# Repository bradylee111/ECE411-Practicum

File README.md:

# ECE411-Practicum

Top project Idea

Spinning music box
mechanically programmable

The idea is to use a photosensor array to read a spinning punch card with light shining through.
Using an ATmega328

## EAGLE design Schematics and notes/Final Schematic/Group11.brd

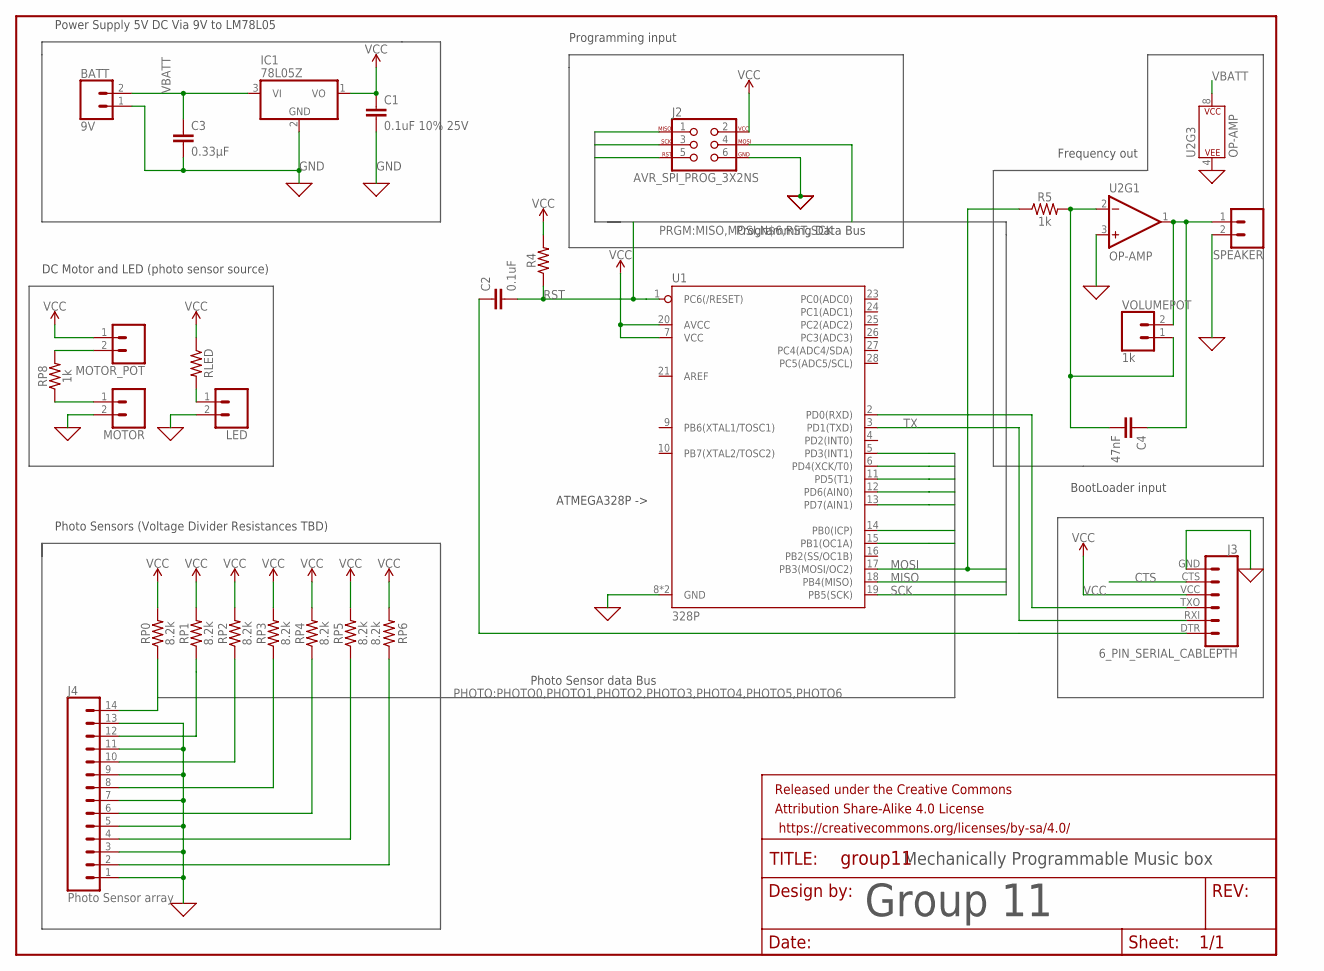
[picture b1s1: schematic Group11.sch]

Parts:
BATT: 9V; 1X02
C1: 0.1uF 10% 25V; 0603
C2: 0.1uF; 0603
C3: 0.33µF; 0805
C4: 47nF; 0603
FRAME1: FRAME-LETTER; CREATIVE_COMMONS
IC1: 78L05Z; TO92
J2: AVR_SPI_PROG_3X2NS; 2X3-NS
J3: 6_PIN_SERIAL_CABLEPTH; FTDI_BASIC
J4: Photo Sensor array; 1X14
LED: CONN_02; 1X02
MOTOR: CONN_02; 1X02
MOTOR_POT: CONN_02; 1X02
R4: 0805
R5: 1k; 0603
RLED: 0603
RP0, RP1, RP2, RP3, RP4, RP5, RP6: 8.2k; 0603
RP8: 1k; 0603
SPEAKER: CONN_02; 1X02
U1: 328P; DIP28
U2: OP-AMP; DIP08
VOLUMEPOT: 1k; 1X02

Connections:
CTS: J3.CTS (5)
GND: BATT.1, C1.2, C3.2, IC1.2 (GND), J2.6, J3.GND (6), J4.1, J4.3, J4.5, J4.7, J4.9, J4.11, J4.13, LED.2, MOTOR.2, SPEAKER.2, U1.8 (GND), U1.22 (GND), U2.3 (+IN), U2.4 (P$V-)
MISO: J2.1, U1.18 (PB4(MISO))
MOSI: J2.4, R5.1, U1.17 (PB3(MOSI/OC2))
unnamed: MOTOR_POT.2, RP8.2
unnamed: LED.1, RLED.2
unnamed: J3.TXO (3), U1.2 (PD0(RXD))
unnamed: C2.1, J3.DTR (1)
unnamed: MOTOR.1, RP8.1
unnamed: C4.2, R5.2, U2.2 (-IN), VOLUMEPOT.1
unnamed: C4.1, SPEAKER.1, U2.1 (OUT), VOLUMEPOT.2
PHOTO0: J4.14, RP0.1, U1.5 (PD3(INT1))
PHOTO1: J4.12, RP1.1, U1.6 (PD4(XCK/T0))
PHOTO2: J4.10, RP2.1, U1.11 (PD5(T1))
PHOTO3: J4.8, RP3.1, U1.12 (PD6(AIN0))
PHOTO4: J4.6, RP4.1, U1.13 (PD7(AIN1))
PHOTO5: J4.4, RP5.1, U1.14 (PB0(ICP))
PHOTO6: J4.2, RP6.1, U1.15 (PB1(OC1A))
RST: C2.2, J2.5, R4.1, U1.1 (PC6(/RESET))
SCK: J2.3, U1.19 (PB5(SCK))
TX: J3.RXI (2), U1.3 (PD1(TXD))
VBATT: BATT.2, C3.1, IC1.3 (VI), U2.8 (P$V+)
VCC: C1.1, IC1.1 (VO), J2.2, J3.VCC (4), MOTOR_POT.1, R4.2, RLED.1, RP0.2, RP1.2, RP2.2, RP3.2, RP4.2, RP5.2, RP6.2, U1.7 (VCC), U1.20 (AVCC)

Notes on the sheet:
Photo Sensors (Voltage Divider Resistances TBD)
DC Motor and LED (photo sensor source)
Programming input
Power Supply 5V DC Via 9V to LM78L05
BootLoader input
Frequency out
ATMEGA328P ->
Photo Sensor data Bus
Programming Data Bus
Group 11
Mechanically Programmable Music box

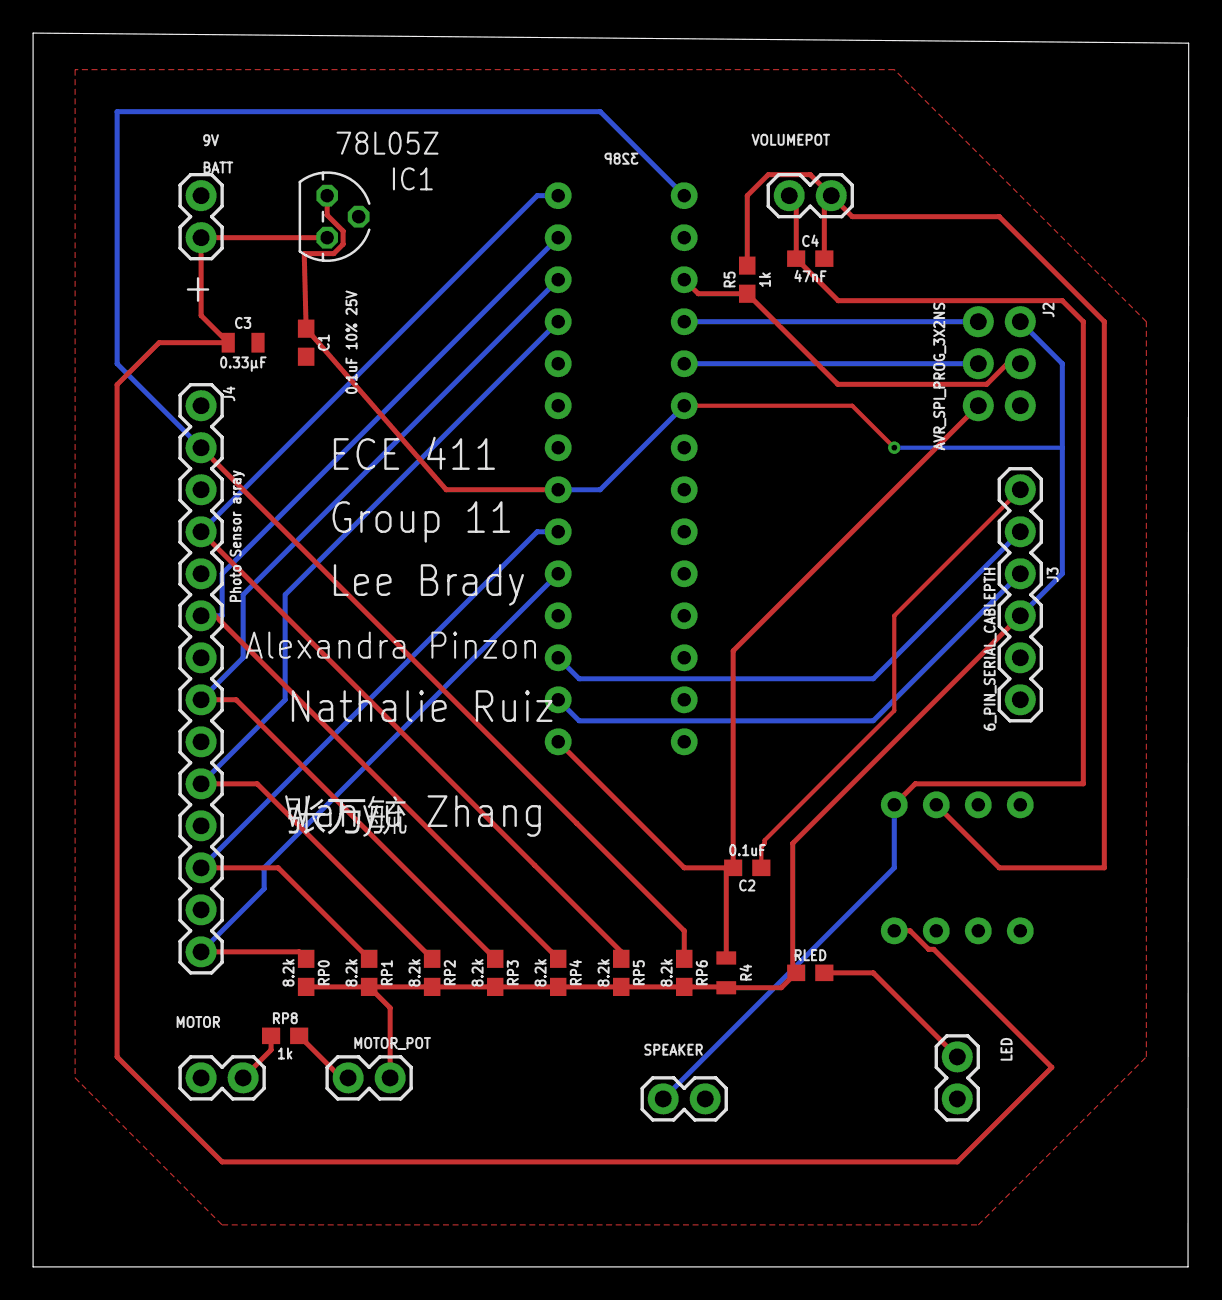
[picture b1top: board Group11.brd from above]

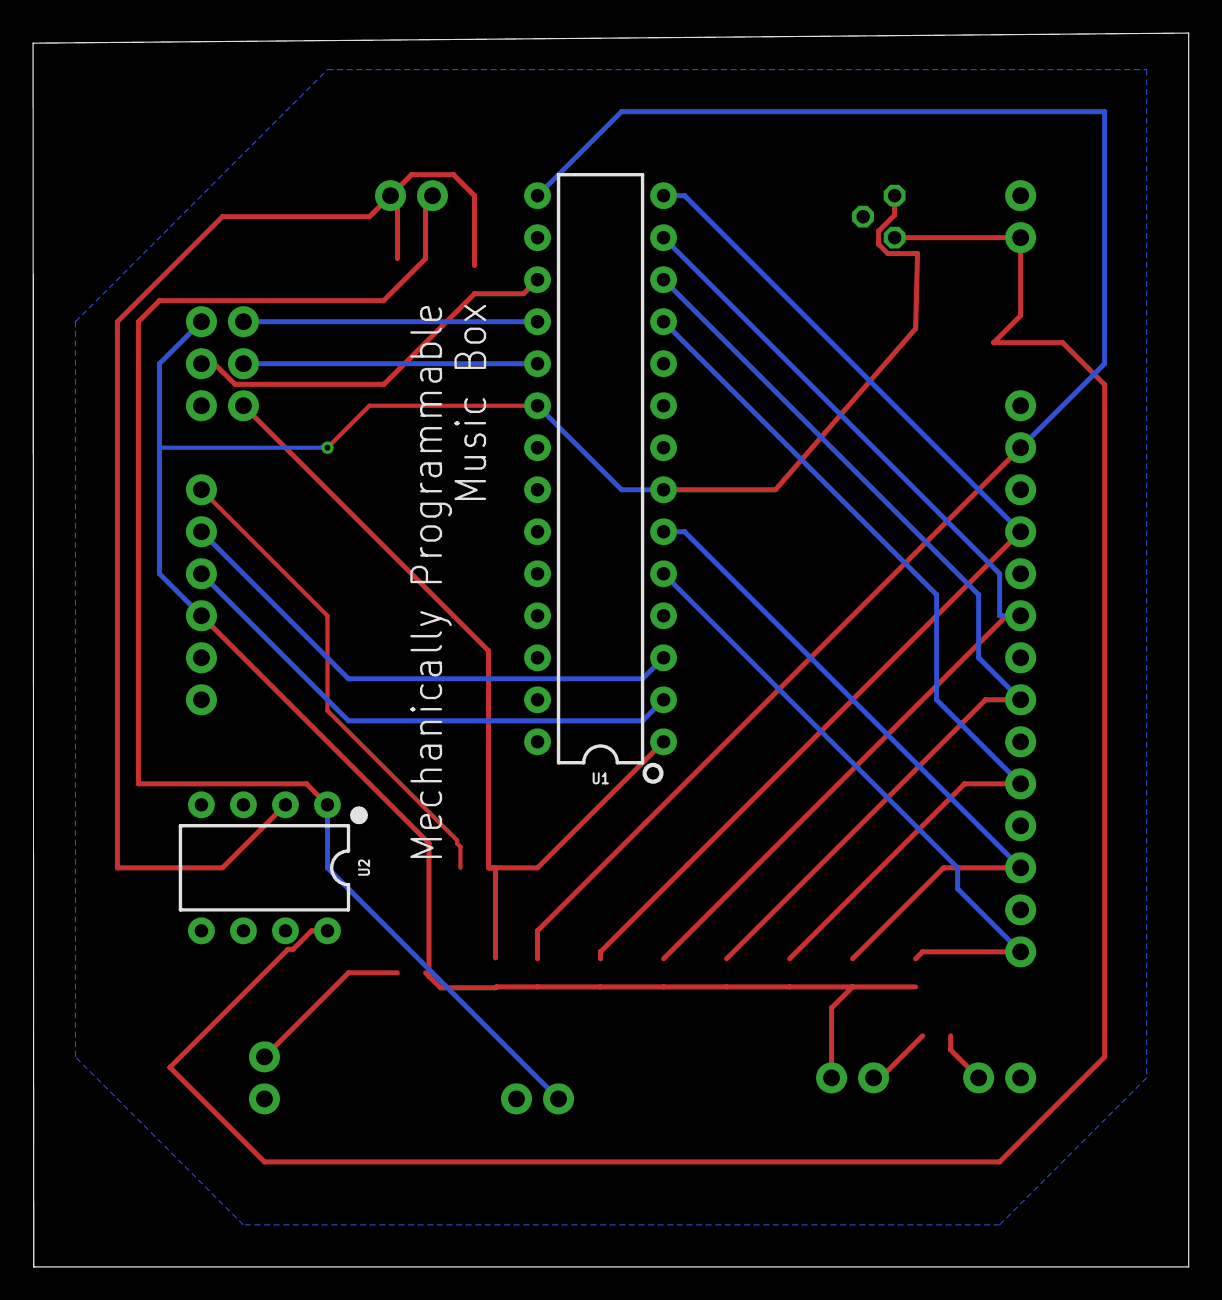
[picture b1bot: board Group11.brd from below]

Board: 2 copper layers, 69.9 x 74.6 mm, 28 parts (2 on the bottom side), 22 nets.

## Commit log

2018-10-14 Meeting 2
2018-10-14 Update Meeting 2
2018-10-14 Create Note
2018-10-19 Create Mini meeting (Alex & Wanyu)
2018-10-20 Create Meeting 3
2018-10-23 Create Eagle Oct 22
2018-10-23 Create Post
2018-10-24 Create Note Lookup
2018-10-24 Create ...
2018-10-24 Update Note Lookup
2018-11-04 Create Updated Power supply
2018-11-05 Create Meeting Notes 11 4
2018-12-03 Create Final schematic images

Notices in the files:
parts and their libraries:
SparkFun-IC-Microcontroller: Licensing: Creative Commons ShareAlike 4.0 International - https://creativecommons.org/licenses/by-sa/4.0
SparkFun-Aesthetics: Released under the Creative Commons Attribution Share-Alike 4.0 License
SparkFun-Aesthetics: https://creativecommons.org/licenses/by-sa/4.0
